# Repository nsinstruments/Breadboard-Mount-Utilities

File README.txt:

Breadboard Utilities
====================
This is a collection of utilities in the form of PCBs mounted on a breadboard,
which distributes power to each. I've used them for testing and development
over the last few years.

These are being released at your own risk, with no warranty or support, and
while they have been useful to me, New Systems Instruments does not warrant
their usefulness or fitness for any particular purpose or any other implied
warranty.

If you need help, please post in one of the usual public forums (discord, mw,
etc.) and @ me. I'm a helpful kind of human, so I might respond, but
unfortunately these aren't commercial products and I can't commit to always
giving support.

This work is licensed under the Creative Commons Attribution-ShareAlike 4.0
International License. To view a copy of this license, visit
http://creativecommons.org/licenses/by-sa/4.0/ or send a letter to Creative
Commons, PO Box 1866, Mountain View, CA 94042, USA.

A few things in here are the work of others, and AFAIK are freely
distributable and compatible with that license, but these retain their
original terms of distribution. I do not consider this a relicensing or any
alteration significant enough to claim some part of copyright on those files.

Since the DIY community is often considerate of personal wishes beyond the
official legal requirements, know that I'm perfectly happy for anyone who
wishes to build these for any purpose, personal commercial or otherwise, to
produce and distribute them to others, to fork the repository and offer
improvements, etc., as long as the terms of the above license are met. If
you're doing something that I might think is neat, or that I might want to
tell other people about, get in touch.

See the individual Read Me files for more details on each board.

Breadboard Compatibility
------------------------
This works with common 0.1" pitch breadboards. Note that AFAIK there is no
fixed standard for breadboards, so there is no guarantee it will work with any
particular breadboard. The most common incompatibility I've seen is where the
rail pins are not aligned with the main pins of the breadboard.

The power is put on the rails as follows:

-12 GND ... GND +12

As I have not seen any standard breadboard which is labeled this way, it is
recommended that you write over the +/- symbols on your breadboard with a
permanent marker to avoid confusion.

Some General Notes on Parts and Assembly
----------------------------------------
Distributors and part numbers are listed on each BOM, but none of this is
sacred; use your good sense to make substitutions as appropriate. In
particular, you might just want to buy some strips of breakable pin headers
rather than a bunch of different lengths.

In soldering these together, it's probably best to first solder the mounting
pins. I did this with the pins inserted in the breadboard, to make up for any
misalignments, but if you do that be careful not to put too much heat in and
melt the breadboard.

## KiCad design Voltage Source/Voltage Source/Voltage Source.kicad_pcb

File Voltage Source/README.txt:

Voltage Source
==============
This is a breadboard mounted dual precision voltage source, switchable between
0V, 3V, and 5v. It is designed to work with the breadboard mounted power
supply in this repository.

Power and Compatibility
-----------------------
This is designed to be powered by breadboard rails with the following
voltages:

-12 GND ... GND +12

This works with common 0.1" pitch breadboards. Note that AFAIK there is no
fixed standard for breadboards, so there is no guarantee it will work with any
particular breadboard. The most common incompatibility I've seen is where the
rail pins are not aligned with the main pins of the breadboard.

Calibration
-----------
This uses precise voltage sources and potentiometers to calibrate an output
voltage to very exact standards, within half a millivolt or so. You can
momentarily get better (within 10 microvolts), but this won't necessarily
stick around with with the mechanical settling of the trimmers or with
temperature changes. The resulting voltage will only be as accurate as your
multimeter, so make sure your multimeter will measure according to your
requirements. Go through each voltage one at a time, and turn the appropriate
potentiometer until the output is satisfactorily close to the nominal value.
You may get better accuracy by going through each voltage a second time, as
the voltage sources may shift very slightly with a slightly changing load.
This will also give the parts time to warm up to their typical operating
temperature. You might need to recalibrate as the trimmers settle.

Accuracy
---------
After calibration, there are three significant remaining sources of
inaccuracy. First, the voltage references themselves contribute a small
temperature dependency of 50ppm per degree C (or whatever is specified for the
particular part you are using). This figure is multiplied by the ratio of the
output voltage to the reference voltage (2.5V). Second, the potentiometers
contribute a temperature dependency. Last, the op amp offset and bias current
both have a temperature dependency. The op amp offset change with temperature
will be reproduced multiplied by the ratio of the output voltage to the
reference voltage. The op amp bias change with temperature will be reproduced
multiplied by the very large source resistors, so it is highly recommended
that you only use FET input op amps.

Resistor values
---------------
The calibration range is set by a resistor in series with the wiper of each
trimmer. These are chosen based on the accuracy of the resistors, op amp, and
voltage sources specified in the BOM. If you substitute components with lower
accuracies, you'll need to adjust the value of these resistors.

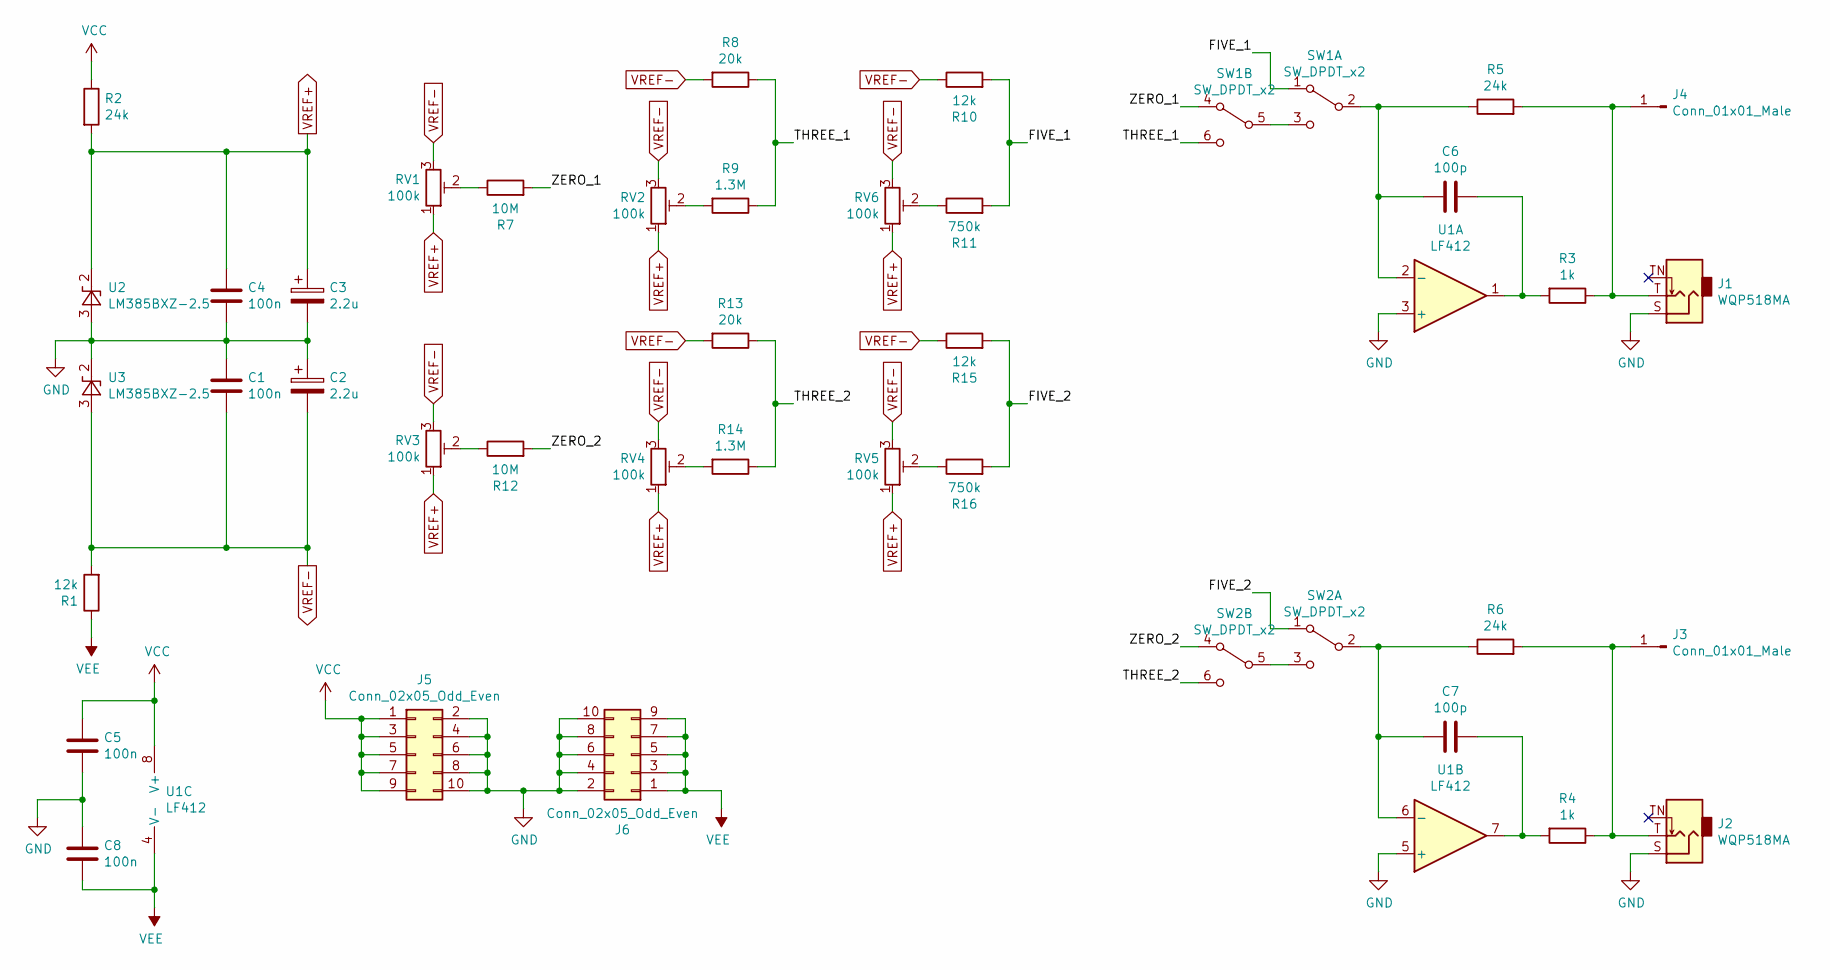
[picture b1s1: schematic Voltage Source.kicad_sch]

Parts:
C1, C4, C5, C8: 100n; C_Disc_D4.7mm_W2.5mm_P5.00mm
C2, C3: 2.2u; CP_Radial_D5.0mm_P2.00mm
C6, C7: 100p; C_Disc_D4.7mm_W2.5mm_P5.00mm
J1, J2: WQP518MA; QingPu_WQP518MA
J3, J4: Conn_01x01_Male; PinHeader_1x01_P2.54mm_Vertical
J5, J6: Conn_02x05_Odd_Even; PinHeader_2x05_P2.54mm_Vertical
R1, R10, R15: 12k; R_Axial_DIN0207_L6.3mm_D2.5mm_P2.54mm_Vertical
R2, R5, R6: 24k; R_Axial_DIN0207_L6.3mm_D2.5mm_P2.54mm_Vertical
R3, R4: 1k; R_Axial_DIN0207_L6.3mm_D2.5mm_P2.54mm_Vertical
R7, R12: 10M; R_Axial_DIN0207_L6.3mm_D2.5mm_P2.54mm_Vertical
R8, R13: 20k; R_Axial_DIN0207_L6.3mm_D2.5mm_P2.54mm_Vertical
R9, R14: 1.3M; R_Axial_DIN0207_L6.3mm_D2.5mm_P2.54mm_Vertical
R11, R16: 750k; R_Axial_DIN0207_L6.3mm_D2.5mm_P2.54mm_Vertical
RV1, RV2, RV3, RV4, RV5, RV6: 100k; Potentiometer_Bourns_3296Y_Vertical
SW1, SW2: SW_DPDT_x2; SW_Sub_DPDT
U1: LF412; DIP-8_W7.62mm
U2, U3: LM385BXZ-2.5; TO-92_Inline

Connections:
/FIVE_1: R10.2, R11.2, SW1.1 (A)
/FIVE_2: R15.2, R16.2, SW2.1 (A)
/THREE_1: R8.1, R9.1, SW1.6 (C)
/THREE_2: R13.1, R14.1, SW2.6 (C)
/ZERO_1: R7.2, SW1.4 (A)
/ZERO_2: R12.2, SW2.4 (A)
GND: C1.1, C2.1, C3.2, C4.2, C5.2, C8.1, J1.S, J2.S, J5.2, J5.4, J5.6, J5.8, J5.10, J6.2, J6.4, J6.6, J6.8, J6.10, U1.3 (+), U1.5 (+), U2.3 (A), U3.2 (K)
unnamed: C6.1, R3.2, U1.1
unnamed: C7.1, R4.2, U1.7
unnamed: J2.T, J3.1 (Pin_1_1), R4.1, R6.2
unnamed: J1.T, J4.1 (Pin_1_1), R3.1, R5.2
unnamed: R7.1, RV1.2
unnamed: R9.2, RV2.2
unnamed: R11.1, RV6.2
unnamed: R12.1, RV3.2
unnamed: R14.2, RV4.2
unnamed: R16.1, RV5.2
unnamed: C6.2, R5.1, SW1.2 (B), U1.2 (-)
unnamed: SW1.3 (C), SW1.5 (B)
unnamed: C7.2, R6.1, SW2.2 (B), U1.6 (-)
unnamed: SW2.3 (C), SW2.5 (B)
VCC: C5.1, J5.1, J5.3, J5.5, J5.7, J5.9, R2.1, U1.8 (V+)
VEE: C8.2, J6.1, J6.3, J6.5, J6.7, J6.9, R1.1, U1.4 (V-)
VREF+: C3.1, C4.1, R2.2, RV1.1, RV2.1, RV3.1, RV4.1, RV5.1, RV6.1, U2.2 (K)
VREF-: C1.2, C2.2, R1.2, R8.2, R10.1, R13.2, R15.1, RV1.3, RV2.3, RV3.3, RV4.3, RV5.3, RV6.3, U3.3 (A)

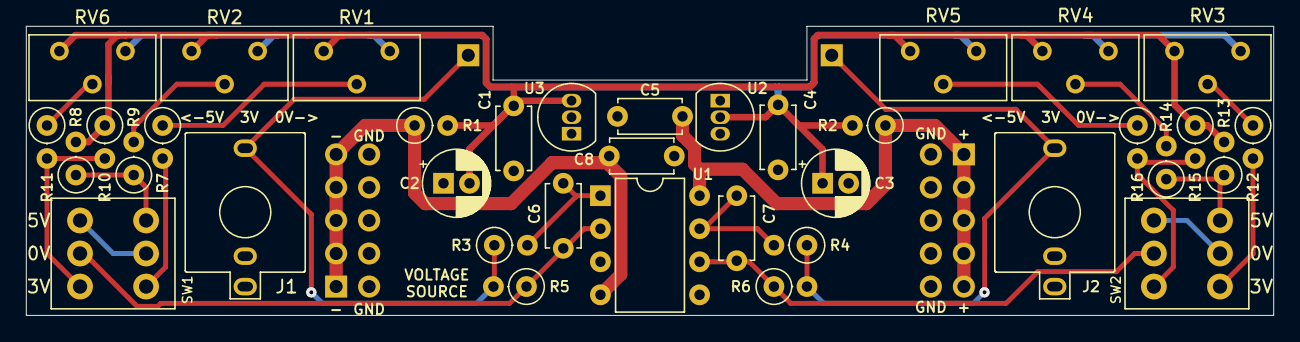
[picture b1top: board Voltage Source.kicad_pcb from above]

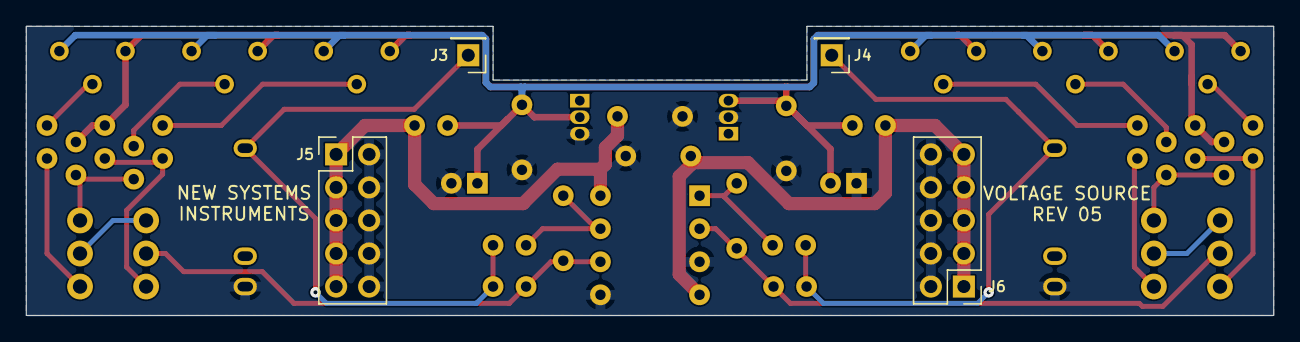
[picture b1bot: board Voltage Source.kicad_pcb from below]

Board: 2 copper layers, 95.9 x 22.2 mm, 41 parts (4 on the bottom side), 25 nets.

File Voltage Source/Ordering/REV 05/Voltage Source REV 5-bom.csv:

Reference,Value,Manufacturer,Part No.,Quantity
C1 C4 C5 C8,100n,Vishay,K104K15X7RF5TH5,4
C6 C7,100p,Vishay,K101J15C0GF5TH5,2
C2 C3,2.2u,Nichicon,UPS1V22 MDD,2
J3 J4,Conn_01x01_Male,Harwin,M20-9770242,1
J5 J6,Conn_02x05_Odd_Even,Harwin,M20-9760542,2
R1,12k,Yageo,MFR-25FRF52-12K,2
R3 R4,1k,Yageo,MFR-25FRF52-1K,2
R2 R5 R6,24k,Yageo,MFR-25FRF52-24K,2
R7 R12,10M,Yageo,HHV-25FR-52-10M,2
R8 R13,20k,Yageo,MFR-25FRF52-20K,2
R9 R14,1.3M,Yageo,MFR-25FRF52-1M3,2
R10 R15,12k,Yageo,MFR-25FRF52-12K,2
R11 R16,750k,Yageo,MFR-25FRF52-750K,2
RV1 RV2 RV3 RV4 RV5 RV6,100k,TT Electronics,67YR100K,6
U1,LF412,Texas Instruments,LF412CP,1
U2 U3,LM385BXZ-2.5,Texas Instruments,LM385BXZ-2.5/NOPB,2
,,,,
J1 J2,3.5mm Jack,Qing Pu,WQP518MA,2
SW1 SW2,DPDT,Taiway/Various,Sub-Miniature DPDT ON-ON-ON Toggle,2

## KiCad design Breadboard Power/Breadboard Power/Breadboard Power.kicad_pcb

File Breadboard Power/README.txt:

Breadboard Power
================
This is a power supply for a breadboard, providing +12V -12V and ground. It is
designed to be robust, simple, repairable, and safe.

Power Capabilities
------------------
This consists of a standard half-wave rectifier circuit powered from 12 VAC
from a wall wart power supply. Since the 12VAC is powering both the +12VDC and
-12VDC rail, the total current requirements will be roughly the sum of the
current on both rails. The recommended 500mA wall wart will provide about
200-250mA per rail before degrading. There is also a 1000mA wall wart
available that would be able to provide more current. However, consider
carefully whether you actually want your breadboard, or any wires sticking out
of it, to be able to deliver enough current to catch components on fire.

Noise and Precision
-------------------
This uses high quality linear LDO regulators and an AC input, resulting
in low ripple at 60Hz, without significant harmonic content at high
frequencies. I haven't done any robust measurements, but it seems to have
ripple within about 500uV at low loads, up to 1-2mV at high loads. So long as
the reservoir capacitor doesn't dip below the drop out ratings for the
regulators.

Compatibility and Location of the Rails
---------------------------------------
The power is put on the rails as follows:

-12 GND ... GND +12

As I have not seen any standard breadboard which is labeled this way, it is
recommended that you write over the +/- symbols on your breadboard with a
permanent marker.

This works with common 0.1" pitch breadboards. Note that AFAIK there is no
fixed standard for breadboards, so there is no guarantee it will work with any
particular breadboard. The most common incompatibility I've seen is where the
rail pins are not aligned with the main pins of the breadboard.

Safety
------
As a DIY project, I cannot possibly provide any guarantees that the finished
device will be safe. As with any unshielded electrical device, there is a small
risk of shock or fire under certain circumstances.

Nevertheless, this power supply is designed with safety and robustness in mind.
Resettable fuses placed between the reservoir capacitors and the regulators
will clamp down on overcurrents and shorts. If you trip them, unplug it, count
to 10, and plug it back in. Additionally, the regulators themselves have
internal current limiters that might catch on before the fuses. Additionally,
there are zeners to prevent overvoltage, which, depending on how bad the
overvoltage is, will trip those same fuses. And of course the power itself is
coming from the isolated secondary of a transformer.

Ordering and Assembly
---------------------
I won't go into details here. Just a few notes.

* The large capacitors are 3300uF or 3.3mF. The capacitance and ESR is lightly
  related to efficiency and how close to the rated current you can go, but the
  exact value is not particularly important.

* The rectifier diodes are Schottkys, as otherwise the LDOs can get starved
  too easily. The voltage each diode sees is rail to rail at the supply
  capacitors, so don't skimp on a lower breakdown voltage.

* The LEDs are low current, and the resistors into them give very low current,
  resulting in just enough brightness so you can tell that they're on. This
  "barely on" is intentional behavior to lower eye strain when looking at the
  breadboard, but if you want them to be brighter, just lower the value of the
  resistors by half or so. Note that if you substitute higher current LEDs, you might need
  lower value resistors for the LEDs to be visible at all.

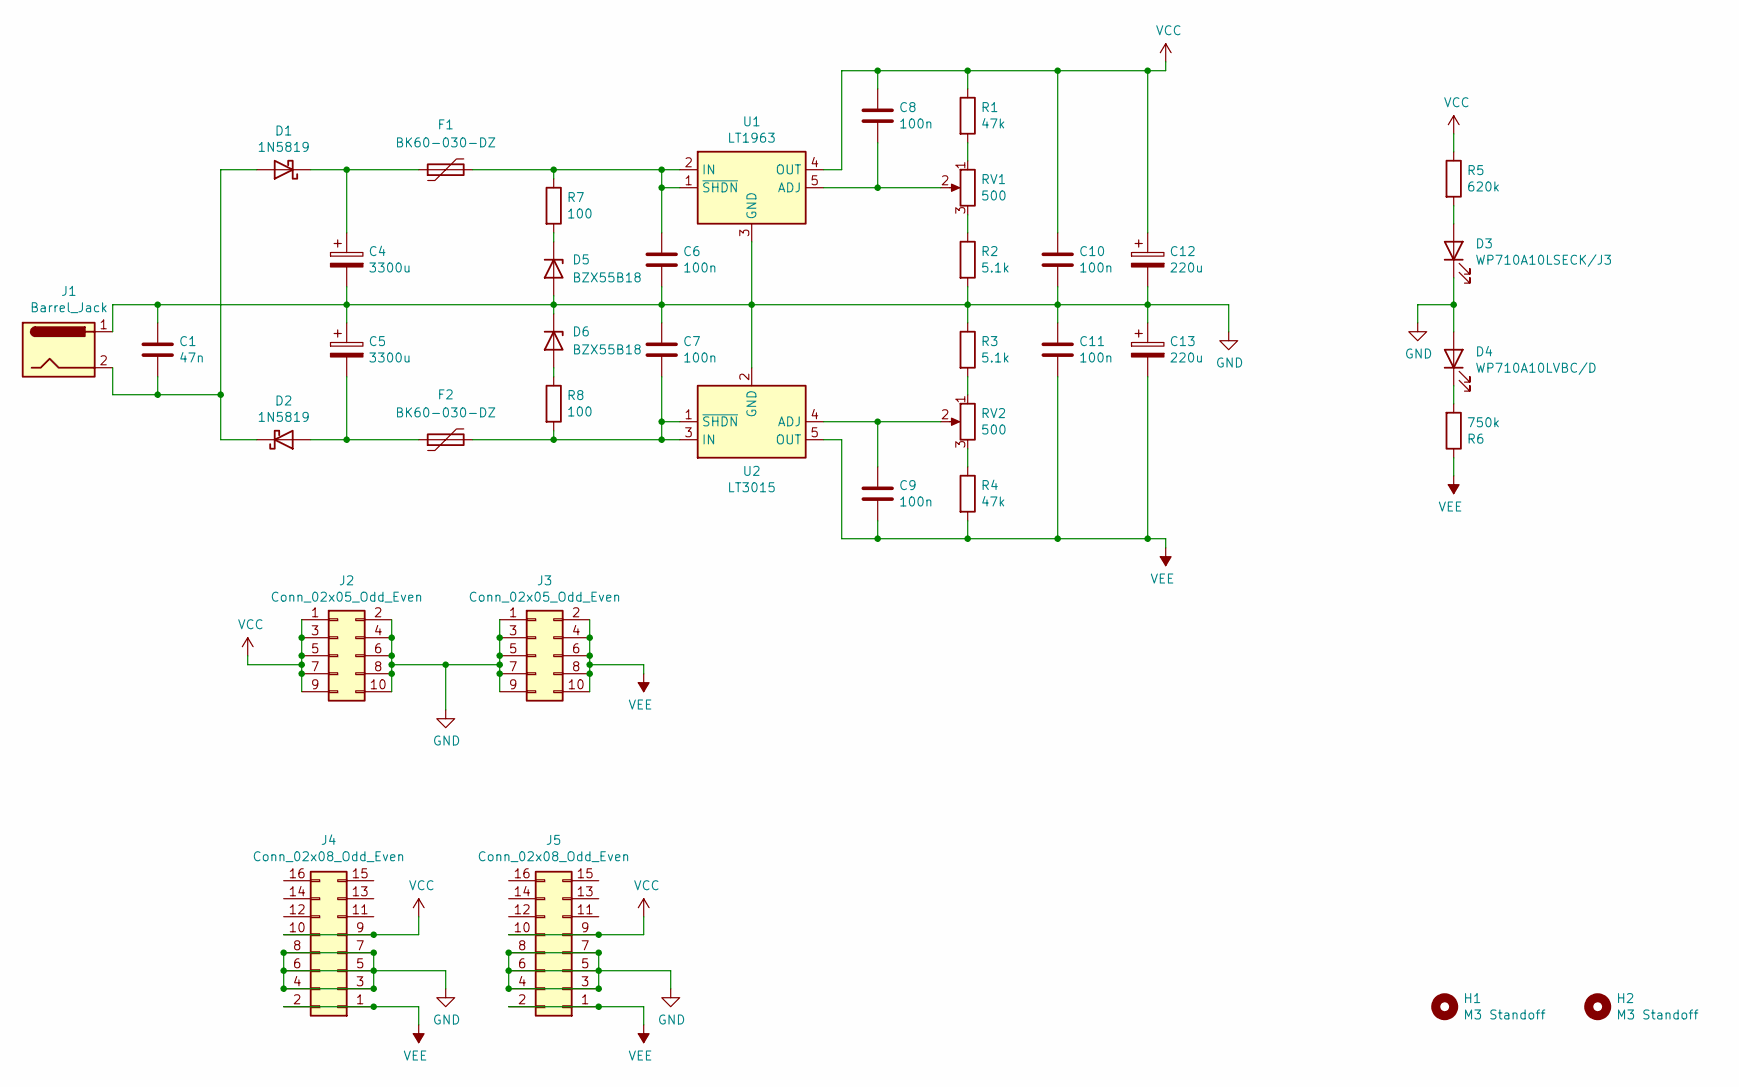
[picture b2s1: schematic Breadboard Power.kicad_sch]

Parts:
C1: 47n; C_Disc_D4.7mm_W2.5mm_P5.00mm
C4, C5: 3300u; CP_Radial_D16.0mm_P7.50mm
C6, C7, C8, C9, C10, C11: 100n; C_Disc_D5.0mm_W2.5mm_P5.00mm
C12, C13: 220u; CP_Radial_D8.0mm_P3.50mm
D1, D2: 1N5819; D_DO-41_SOD81_P7.62mm_Horizontal
D3: WP710A10LSECK/J3; LED_D3.0mm
D4: WP710A10LVBC/D; LED_D3.0mm
D5, D6: BZX55B18; D_DO-35_SOD27_P7.62mm_Horizontal
F1, F2: BK60-030-DZ; C_Disc_D7.5mm_W2.5mm_P5.00mm
H1, H2: M3 Standoff; MountingHole_3.2mm_M3_Pad
J1: Barrel_Jack; BarrelJack_Horizontal
J2, J3: Conn_02x05_Odd_Even; PinHeader_2x05_P2.54mm_Vertical
J4, J5: Conn_02x08_Odd_Even; IDC-Header_2x08_P2.54mm_Vertical
R1, R4: 47k; R_Axial_DIN0207_L6.3mm_D2.5mm_P7.62mm_Horizontal
R2, R3: 5.1k; R_Axial_DIN0207_L6.3mm_D2.5mm_P7.62mm_Horizontal
R5: 620k; R_Axial_DIN0207_L6.3mm_D2.5mm_P7.62mm_Horizontal
R6: 750k; R_Axial_DIN0207_L6.3mm_D2.5mm_P7.62mm_Horizontal
R7, R8: 100; R_Axial_DIN0207_L6.3mm_D2.5mm_P7.62mm_Horizontal
RV1, RV2: 500; Potentiometer_Bourns_3296Y_Vertical
U1: LT1963; TO-220-5_P3.4x3.7mm_StaggerOdd_Lead3.8mm_Vertical
U2: LT3015; TO-220-5_P3.4x3.7mm_StaggerOdd_Lead3.8mm_Vertical

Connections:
GND: C1.1, C4.2, C5.1, C6.2, C7.1, C10.2, C11.1, C12.2, C13.1, D3.1 (K), D4.2 (A), D5.2 (A), D6.1 (K), J1.1, J2.2, J2.4, J2.6, J2.8, J2.10, J3.1, J3.3, J3.5, J3.7, J3.9, J4.3, J4.4, J4.5, J4.6, J4.7, J4.8, J5.3, J5.4, J5.5, J5.6, J5.7, J5.8, R2.2, R3.1, U1.3 (GND), U2.2 (GND)
unnamed: C1.2, D1.2 (A), D2.1 (K), J1.2
unnamed: C4.1, D1.1 (K), F1.1
unnamed: C5.2, D2.2 (A), F2.1
unnamed: D3.2 (A), R5.2
unnamed: D4.1 (K), R6.2
unnamed: D5.1 (K), R7.2
unnamed: D6.2 (A), R8.1
unnamed: R1.2, RV1.1
unnamed: R2.1, RV1.3
unnamed: R3.2, RV2.1
unnamed: R4.1, RV2.3
unnamed: C8.2, RV1.2, U1.5 (ADJ)
unnamed: C6.1, F1.2, R7.1, U1.1 (~SHDN), U1.2 (IN)
unnamed: C9.1, RV2.2, U2.4 (ADJ)
unnamed: C7.2, F2.2, R8.2, U2.1 (~SHDN), U2.3 (IN)
VCC: C8.1, C10.1, C12.1, J2.1, J2.3, J2.5, J2.7, J2.9, J4.9, J4.10, J5.9, J5.10, R1.1, R5.1, U1.4 (OUT)
VEE: C9.2, C11.2, C13.2, J3.2, J3.4, J3.6, J3.8, J3.10, J4.1, J4.2, J5.1, J5.2, R4.2, R6.1, U2.5 (OUT)

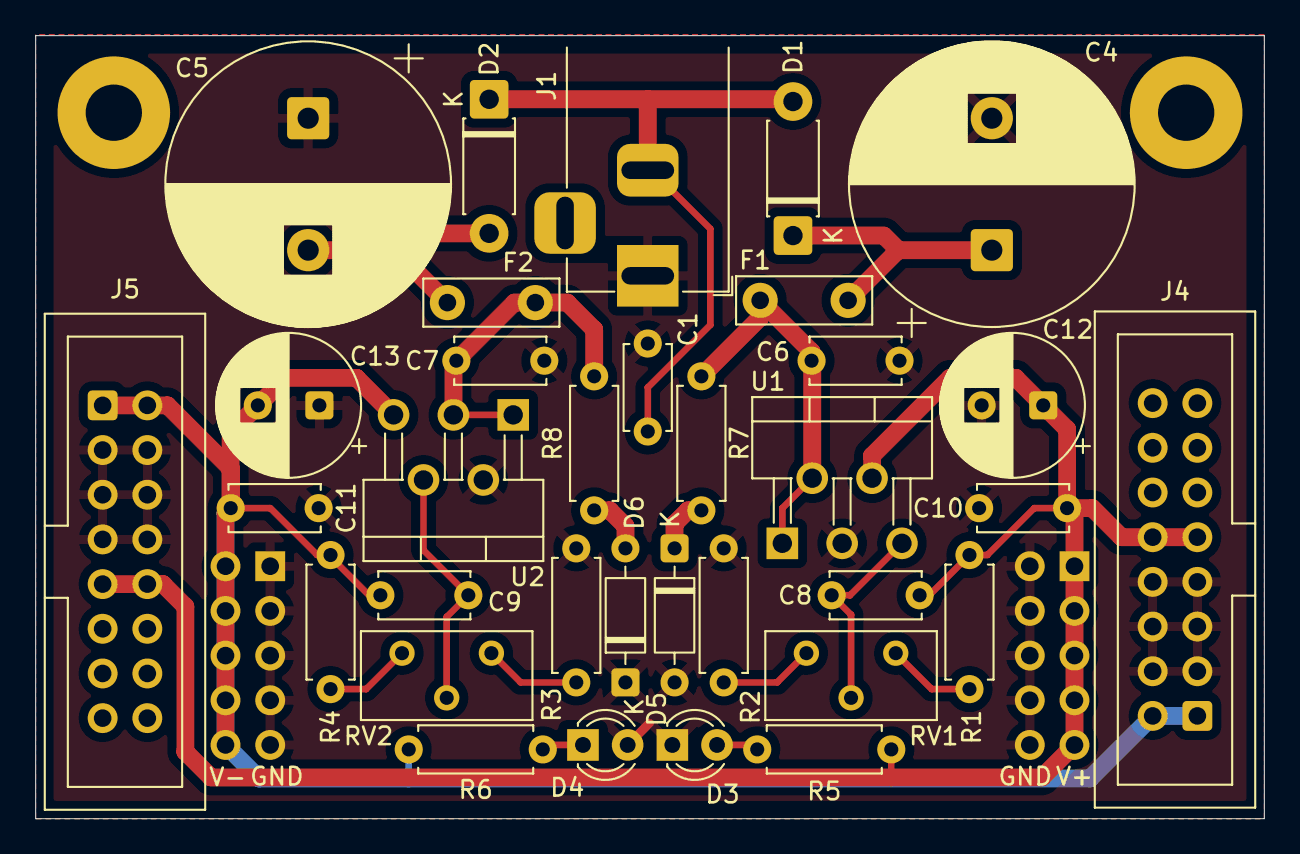
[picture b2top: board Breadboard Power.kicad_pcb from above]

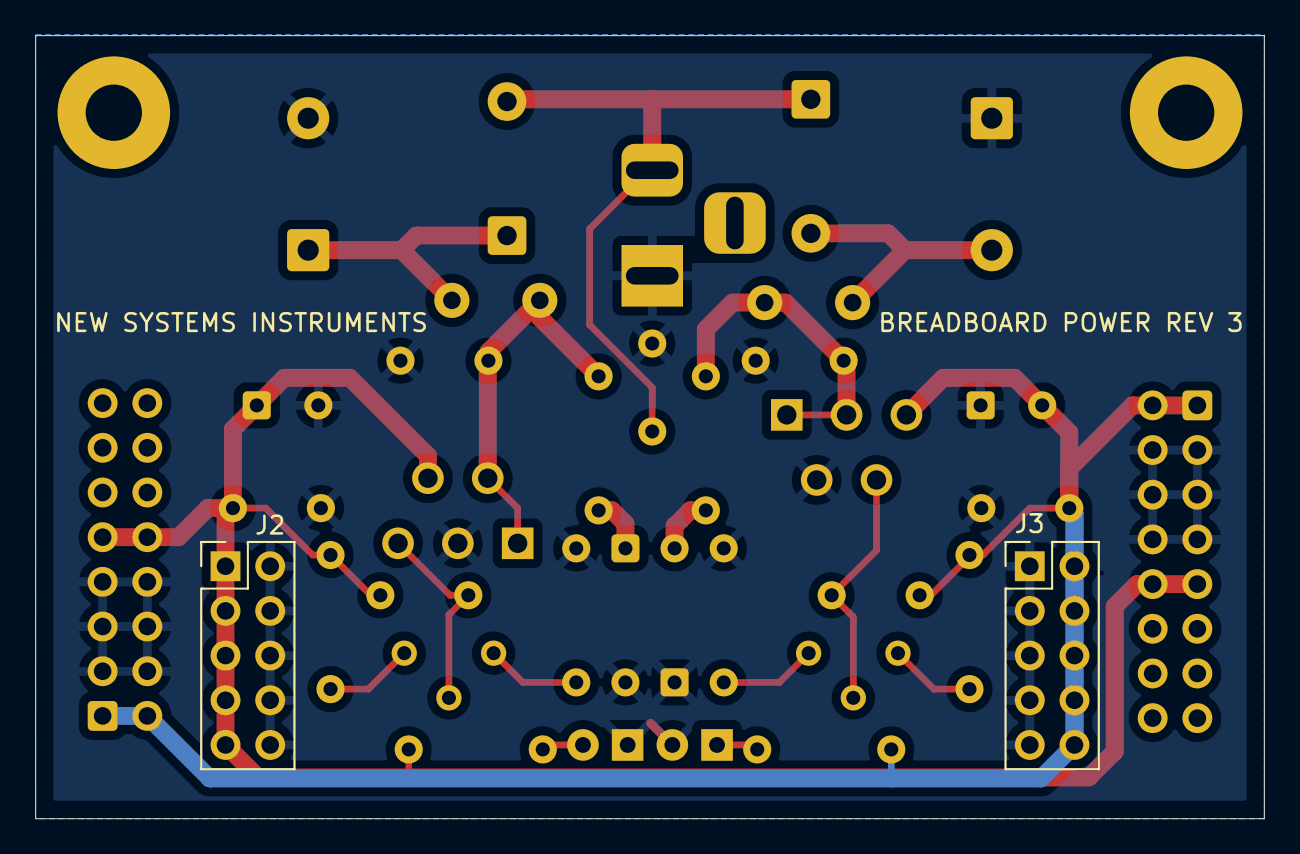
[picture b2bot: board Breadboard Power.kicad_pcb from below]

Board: 2 copper layers, 69.8 x 44.5 mm, 38 parts (2 on the bottom side), 18 nets.

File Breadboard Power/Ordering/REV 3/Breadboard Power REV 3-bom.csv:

Reference,Value,Footprint,Manufacturer,Part No.,Quantity
C1,47n,Capacitor_THT:C_Disc_D4.7mm_W2.5mm_P5.00mm,Vishay,K473K15X7RF5TH5,1
C4 C5,3300u,Capacitor_THT:CP_Radial_D16.0mm_P7.50mm,Nichicon,UPJ1E332MHD,2
C6 C7 C8 C9 C10 C11,100n,Capacitor_THT:C_Disc_D5.0mm_W2.5mm_P5.00mm,Vishay,K104K15X7RF5TH5,6
C12 C13,220u,Capacitor_THT:CP_Radial_D8.0mm_P3.50mm,Nichicon,UPS1E221MPD,2
D1 D2,1N5819,Diode_THT:D_DO-41_SOD81_P7.62mm_Horizontal,ON Semiconductor,1N5819G,2
D3,WP710A10LSECK/J3,LED_THT:LED_D3.0mm,Kingbright,WP710A10LSECK/J3,1
D4,WP710A10LVBC/D,LED_THT:LED_D3.0mm,Kingbright,WP710A10LVBC/D,1
D5 D6,BZX55B18,Diode_THT:D_DO-35_SOD27_P7.62mm_Horizontal,Vishay,BZX55B18,2
F1 F2,BK60-030-DZ,Capacitor_THT:C_Disc_D7.5mm_W2.5mm_P5.00mm,Yageo,BK60-030-DZ,2
J1,Barrel_Jack,Connector_BarrelJack:BarrelJack_Horizontal,Kobiconn,163-179PH-EX,1
J2 J3,Conn_02x05_Odd_Even,Connector_PinHeader_2.54mm:PinHeader_2x05_P2.54mm_Vertical,Harwin,M20-9760542,2
J4 J5,Conn_02x08_Odd_Even,Connector_IDC:IDC-Header_2x08_P2.54mm_Vertical,Adam Tech,BHR-16-VUA,2
R1 R4,47k,Resistor_THT:R_Axial_DIN0207_L6.3mm_D2.5mm_P7.62mm_Horizontal,Yageo,MFR-25FRF52-47K,2
R2 R3,5.1k,Resistor_THT:R_Axial_DIN0207_L6.3mm_D2.5mm_P7.62mm_Horizontal,Yageo,MFR-25FRF52-5K1,2
R5,620k,Resistor_THT:R_Axial_DIN0207_L6.3mm_D2.5mm_P7.62mm_Horizontal,Yageo,MFR-25FRF52-620K,1
R6,750k,Resistor_THT:R_Axial_DIN0207_L6.3mm_D2.5mm_P7.62mm_Horizontal,Yageo,MFR-25FRF52-750K,1
R7 R8,100,Resistor_THT:R_Axial_DIN0207_L6.3mm_D2.5mm_P7.62mm_Horizontal,Yageo,MFR-25FRF52-100R,2
RV1 RV2,500,Potentiometer_THT:Potentiometer_Bourns_3296Y_Vertical,TT Electronics,67YR500,2
U1,LT1963,Package_TO_SOT_THT:TO-220-5_P3.4x3.7mm_StaggerOdd_Lead3.8mm_Vertical,Analog Devices Inc.,LT1963ET#PBF,1
U2,LT3015,Package_TO_SOT_THT:TO-220-5_P3.4x3.7mm_StaggerOdd_Lead3.8mm_Vertical,Analog Devices Inc.,LT3015ET#PBF,1
,12 mm M3 standoffs,,Keystone Electronics,24434,2
,6mm M3 screws,,Keystone Electronics,29311,2
,12 VAC power supply,,Triad,WAU12-500,1

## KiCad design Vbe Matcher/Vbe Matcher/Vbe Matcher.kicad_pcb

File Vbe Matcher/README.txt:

Vbe Matcher
===========
This is a simple widget to match the Vbe on two bipolar transistors. 

Theory of Operation
-------------------
See the document by Ian Fritz in this repository.

Caveat Emptor
-------------
This circuit adequately reproduces the Ian Fritz circuit described in the
paper, along with the added trimmer. If we were breadboarding this circuit,
that would be the end of it. However, given that it's a PCB, practically there
are quite a few nice things that could have been done but weren't. For
example, there could be posts to clip an alligator clip for a multimeter, thus
saving one or two of your four hands. It works, but it isn't streamlined for
ease of use. One of the nice things about the Ian Fritz circuit, however, is
that it's intuitive and simple and easy to understand and modify.

Another thing that I should mention is that you should consider whether the
transistors in question need to have the same Vbe or just the same Vt, or
temperature dependency. Proximity gives you the same Vt, and you don't need to
match. In my case, Vt is usually the important part, and so I don't use this
circuit very often.

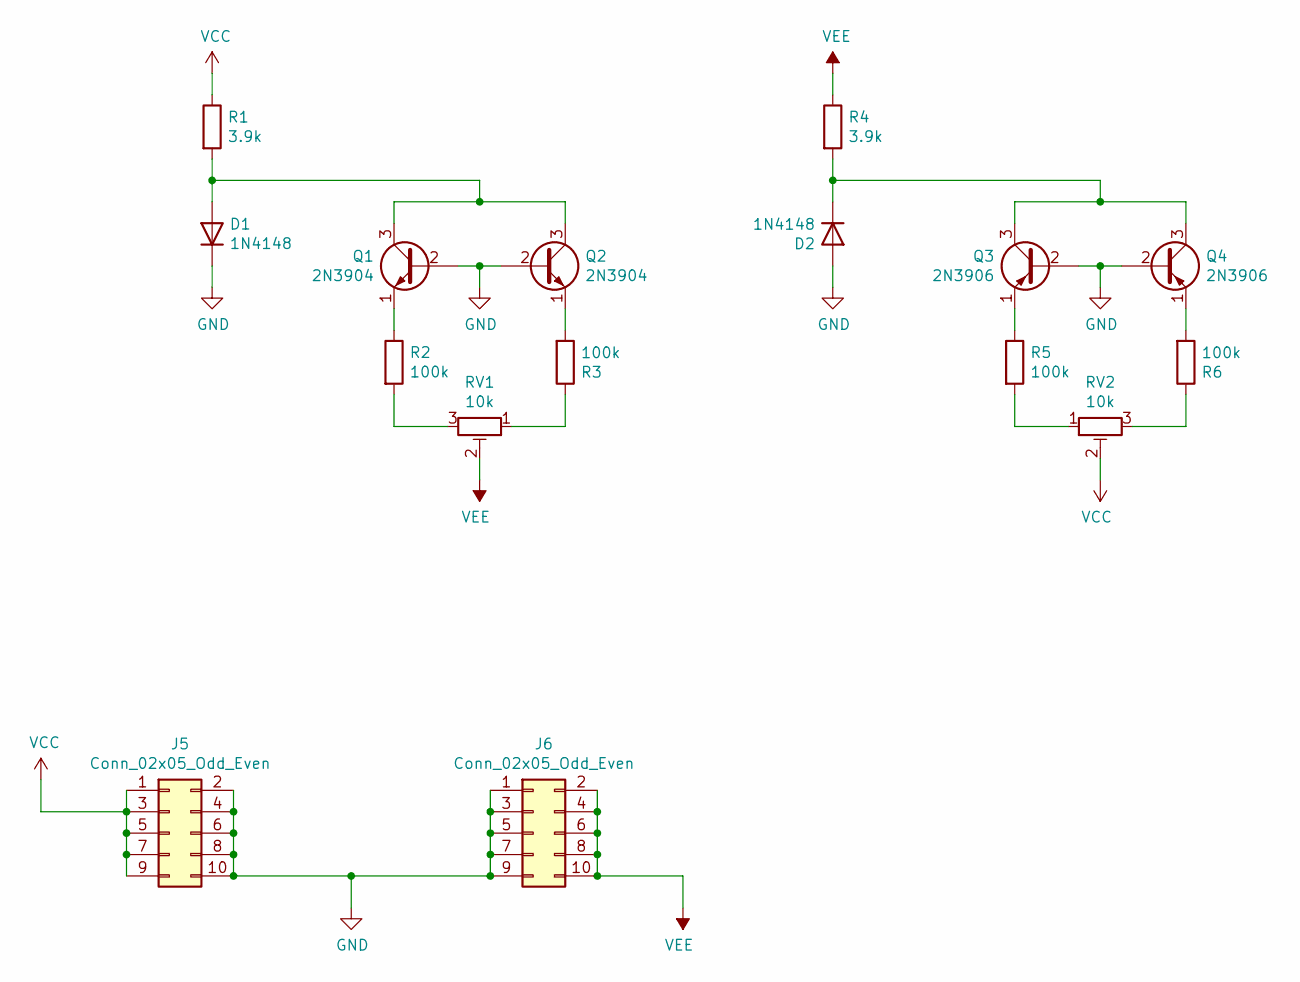
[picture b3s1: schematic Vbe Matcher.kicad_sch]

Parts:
D1, D2: 1N4148; D_DO-35_SOD27_P7.62mm_Horizontal
J5, J6: Conn_02x05_Odd_Even; PinHeader_2x05_P2.54mm_Vertical
Q1, Q2: 2N3904; TO-92_Inline_Wide
Q3, Q4: 2N3906; TO-92_Inline_Wide
R1, R4: 3.9k; R_Axial_DIN0207_L6.3mm_D2.5mm_P7.62mm_Horizontal
R2, R3, R5, R6: 100k; R_Axial_DIN0207_L6.3mm_D2.5mm_P2.54mm_Vertical
RV1, RV2: 10k; Pot_TT_36F

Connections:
GND: D1.1 (K), D2.2 (A), J5.2, J5.4, J5.6, J5.8, J5.10, J6.1, J6.3, J6.5, J6.7, J6.9, Q1.2 (B), Q2.2 (B), Q3.2 (B), Q4.2 (B)
unnamed: D1.2 (A), Q1.3 (C), Q2.3 (C), R1.2
unnamed: D2.1 (K), Q3.3 (C), Q4.3 (C), R4.2
unnamed: Q1.1 (E), R2.1
unnamed: Q2.1 (E), R3.2
unnamed: Q3.1 (E), R5.1
unnamed: Q4.1 (E), R6.2
unnamed: R2.2, RV1.3
unnamed: R3.1, RV1.1
unnamed: R5.2, RV2.1
unnamed: R6.1, RV2.3
VCC: J5.1, J5.3, J5.5, J5.7, J5.9, R1.1, RV2.2
VEE: J6.2, J6.4, J6.6, J6.8, J6.10, R4.1, RV1.2

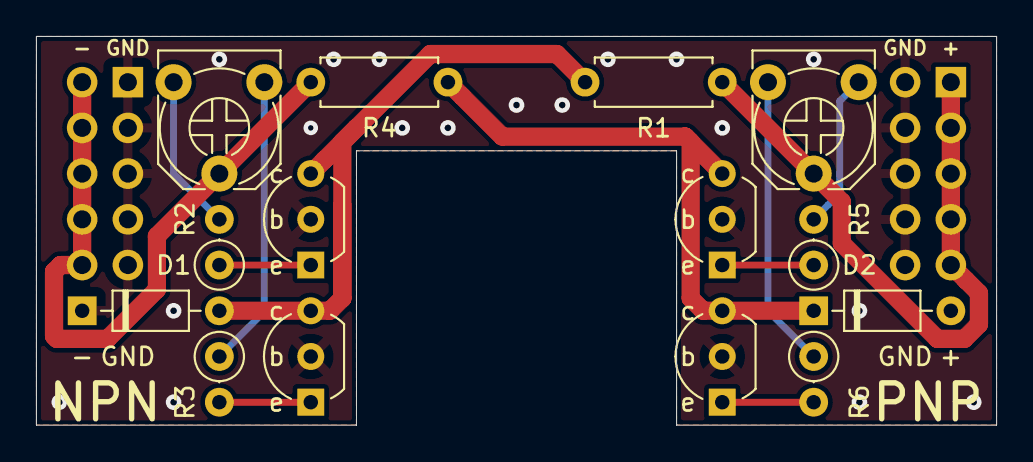
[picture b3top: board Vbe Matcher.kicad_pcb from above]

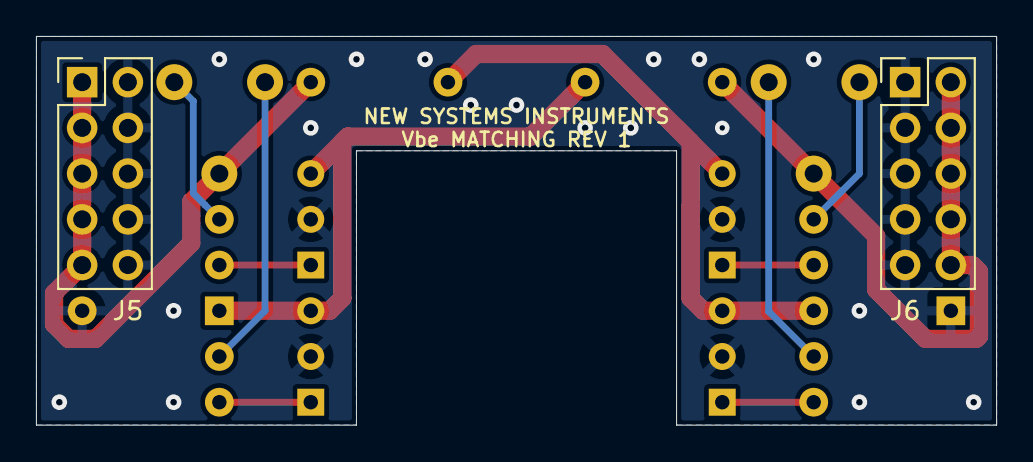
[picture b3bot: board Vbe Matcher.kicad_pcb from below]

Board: 2 copper layers, 53.3 x 21.6 mm, 16 parts (2 on the bottom side), 13 nets.

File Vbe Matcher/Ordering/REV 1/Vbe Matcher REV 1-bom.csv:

Reference,Value,Distributor,Manufacturer,Part No.,Quantity,Price
D1 D2 ,1N4148,Mouser/Digi-Key,ON Semiconductor,1N4148,2,$0.10
J5 J6 ,Conn_02x05_Odd_Even,Mouser/Digi-Key,Harwin,M20-9760542,2,$0.43
Jx,Conn_01x06,Mouser/Digi-Key,Harwin,M20-9770742,2,$0.51
R1 R4 ,3.9k,Mouser/Digi-Key,Yageo,MFR-25FRF52-3K9,2,$0.10
R2 R3 R5 R6 ,100k,Mouser/Digi-Key,Yageo,MFR-25FRF52-100K,4,$0.12
RV1 RV2 ,10k,Mouser/Digi-Key,Bourns,3306F-1-103,2,$0.43

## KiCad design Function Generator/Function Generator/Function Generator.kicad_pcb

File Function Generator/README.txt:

Function Generator
==================
This is a simple breadboard mounted dual function generator, with a range of
3.5 minute cycles to 20kHz and a triangle and square wave output. It is
designed to work with the breadboard mounted power supply in this repository.

Power and Compatibility
-----------------------
This is designed to be powered by breadboard rails with the following
voltages:

-12 GND ... GND +12

This works with common 0.1" pitch breadboards. Note that AFAIK there is no
fixed standard for breadboards, so there is no guarantee it will work with any
particular breadboard. The most common incompatibility I've seen is where the
rail pins are not aligned with the main pins of the breadboard.

Notes on Components
-------------------
* The ceramic capacitors used in the oscillator must be C0G/NP0, but could be
  replaced by film capacitors if they match the footprint.
* The electrolytic capacitors used in the oscillator are bipolar. Unlike in a
  decoupling application, in this circuit a polarized electrolytic would fail,
  possibly rupturing violently.

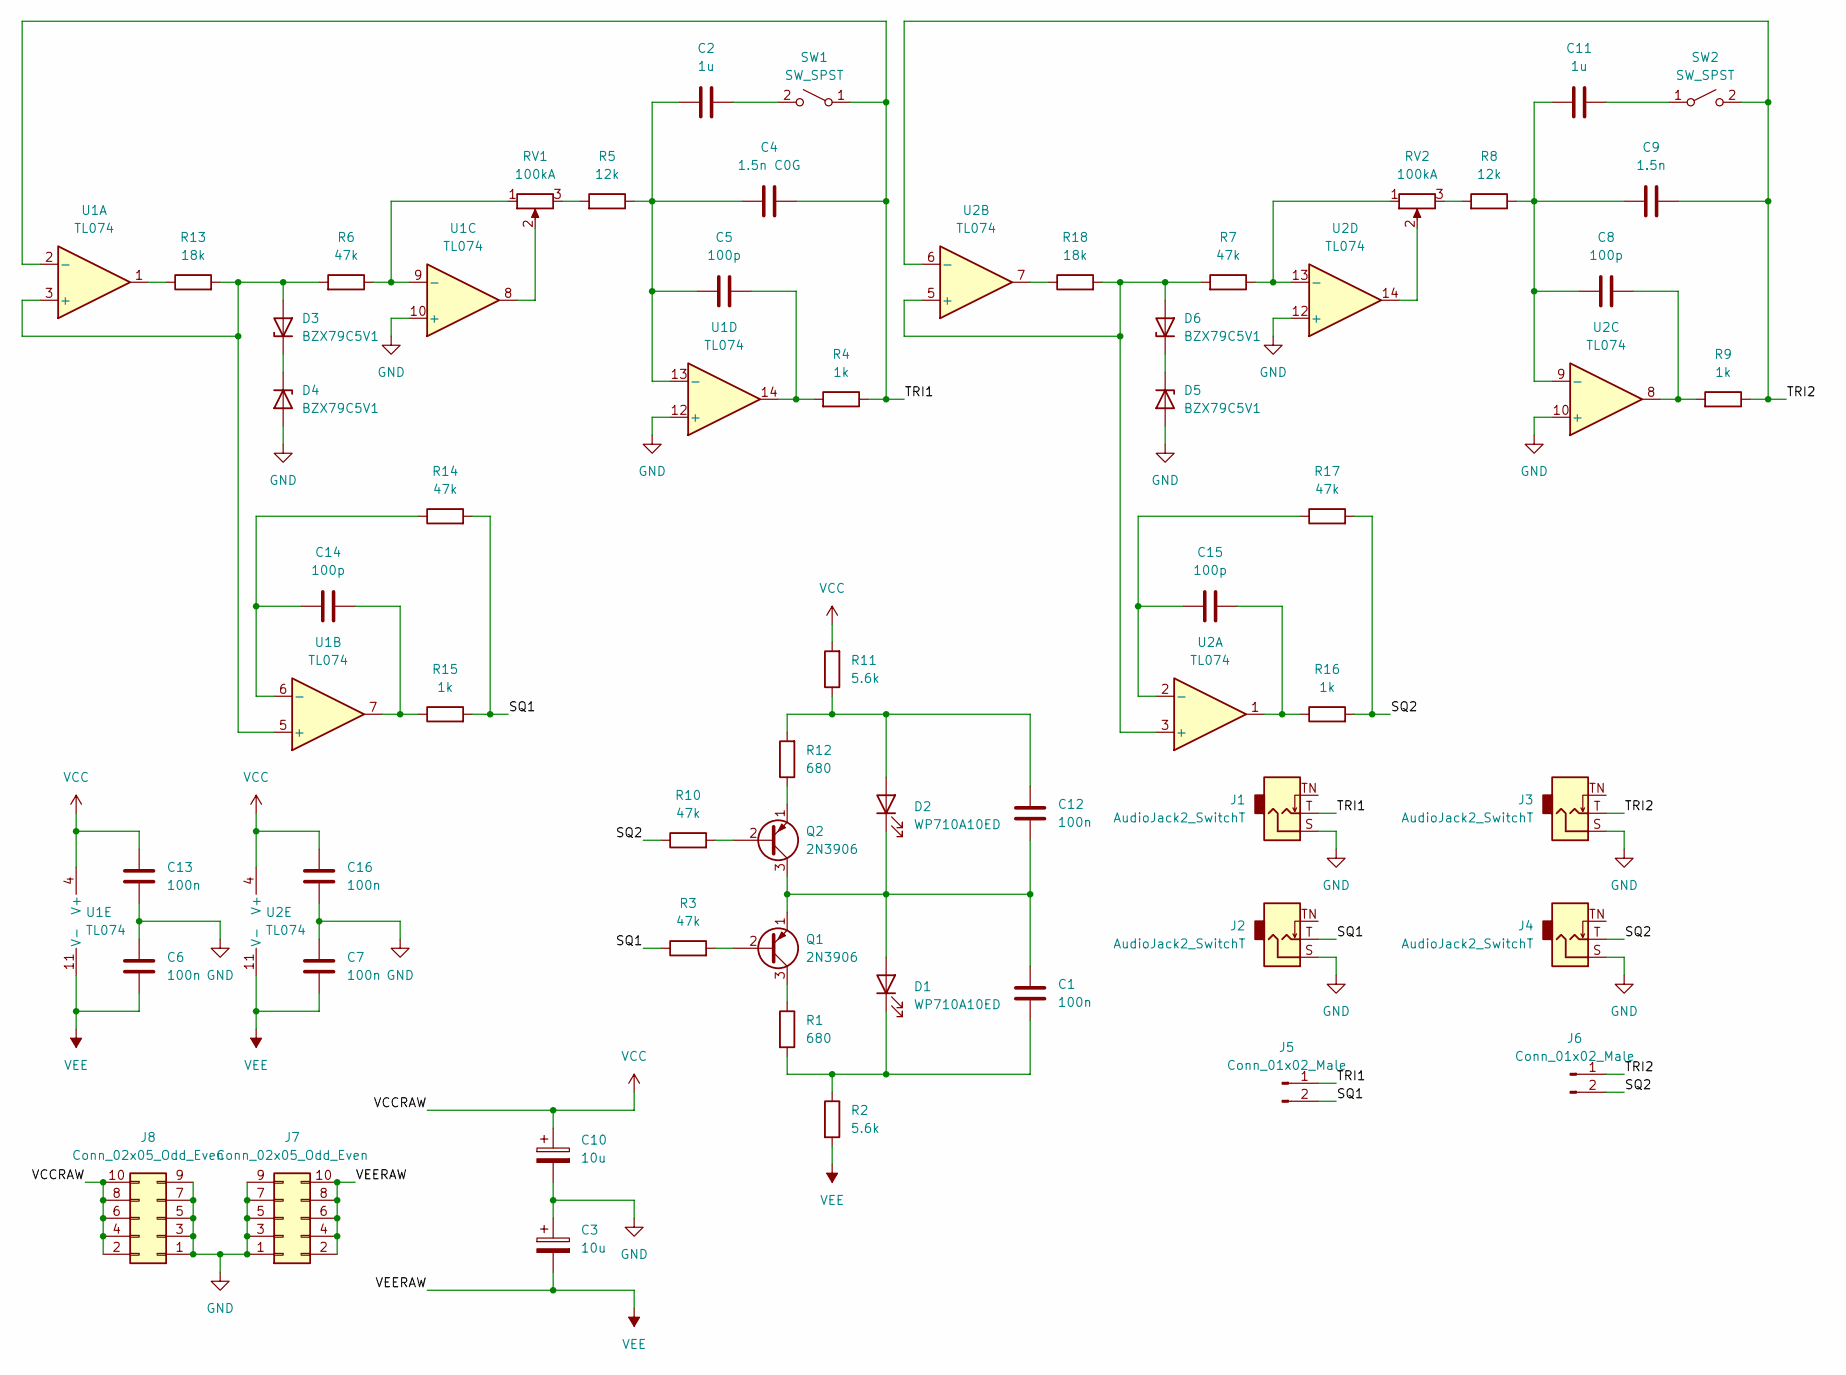
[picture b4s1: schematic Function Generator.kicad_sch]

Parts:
C1, C6, C7, C12, C13, C16: 100n; C_Disc_D4.7mm_W2.5mm_P5.00mm
C2, C11: 1u; C_Radial_D5.0mm_H11.0mm_P2.00mm
C3, C10: 10u; CP_Radial_D5.0mm_P2.00mm
C4: 1.5n C0G; C_Disc_D4.7mm_W2.5mm_P5.00mm
C5, C8, C14, C15: 100p; C_Disc_D4.7mm_W2.5mm_P5.00mm
C9: 1.5n; C_Disc_D4.7mm_W2.5mm_P5.00mm
D1, D2: WP710A10ED; LED_D3.0mm-2
D3, D4, D5, D6: BZX79C5V1; D_DO-35_SOD27_P2.54mm_Vertical_KathodeUp
J1, J2, J3, J4: AudioJack2_SwitchT; QingPu_WQP518MA
J5, J6: Conn_01x02_Male; PinHeader_1x02_P2.54mm_Vertical
J7, J8: Conn_02x05_Odd_Even; PinHeader_2x05_P2.54mm_Vertical
Q1, Q2: 2N3906; TO-92_Inline
R1, R12: 680; R_Axial_DIN0207_L6.3mm_D2.5mm_P2.54mm_Vertical
R2, R11: 5.6k; R_Axial_DIN0207_L6.3mm_D2.5mm_P2.54mm_Vertical
R3, R6, R7, R10, R14, R17: 47k; R_Axial_DIN0207_L6.3mm_D2.5mm_P2.54mm_Vertical
R4, R9, R15, R16: 1k; R_Axial_DIN0207_L6.3mm_D2.5mm_P2.54mm_Vertical
R5: 12k; R_Axial_DIN0207_L6.3mm_D2.5mm_P2.54mm_Vertical
R8: 12k; R_Axial_DIN0207_L6.3mm_D2.5mm_P7.62mm_Horizontal
R13, R18: 18k; R_Axial_DIN0207_L6.3mm_D2.5mm_P2.54mm_Vertical
RV1, RV2: 100kA; Potentiometer_Alpha_RD901F-40
SW1, SW2: SW_SPST; SW_Taiway_Sub_SPDT
U1, U2: TL074; DIP-14_W7.62mm

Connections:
/SQ1: J2.T, J5.2, R3.1, R14.2, R15.2
/SQ2: J4.T, J6.2, R10.1, R16.2, R17.2
/TRI1: C4.2, J1.T, J5.1, R4.1, SW1.1 (A), U1.2 (-)
/TRI2: C9.2, J3.T, J6.1, R9.1, SW2.2 (B), U2.6 (-)
GND: C3.1, C6.1, C7.1, C10.2, C13.2, C16.2, D4.2 (A), D5.2 (A), J1.S, J2.S, J3.S, J4.S, J7.1, J7.3, J7.5, J7.7, J7.9, J8.1, J8.3, J8.5, J8.7, J8.9, U1.10 (+), U1.12 (+), U2.10 (+), U2.12 (+)
unnamed: C1.2, D1.1 (K), R1.2, R2.1
unnamed: C2.2, SW1.2 (B)
unnamed: C2.1, C4.1, C5.1, R5.1, U1.13 (-)
unnamed: C5.2, R4.2, U1.14
unnamed: C8.1, C9.1, C11.1, R8.1, U2.9 (-)
unnamed: C8.2, R9.2, U2.8
unnamed: C11.2, SW2.1 (A)
unnamed: C12.1, D2.2 (A), R11.1, R12.2
unnamed: C1.1, C12.2, D1.2 (A), D2.1 (K), Q1.1 (E), Q2.3 (C)
unnamed: C14.1, R14.1, U1.6 (-)
unnamed: C14.2, R15.1, U1.7
unnamed: C15.1, R17.1, U2.2 (-)
unnamed: C15.2, R16.1, U2.1
unnamed: D3.1 (K), D4.1 (K)
unnamed: D3.2 (A), R6.2, R13.2, U1.3 (+), U1.5 (+)
unnamed: D5.1 (K), D6.1 (K)
unnamed: D6.2 (A), R7.2, R18.2, U2.3 (+), U2.5 (+)
unnamed: Q1.2 (B), R3.2
unnamed: Q1.3 (C), R1.1
unnamed: Q2.1 (E), R12.1
unnamed: Q2.2 (B), R10.2
unnamed: R5.2, RV1.3
unnamed: R6.1, RV1.1, U1.9 (-)
unnamed: R7.1, RV2.1, U2.13 (-)
unnamed: R8.2, RV2.3
unnamed: R13.1, U1.1
unnamed: R18.1, U2.7
unnamed: RV1.2, U1.8
unnamed: RV2.2, U2.14
VCC: C10.1, C13.1, C16.1, J8.2, J8.4, J8.6, J8.8, J8.10, R11.2, U1.4 (V+), U2.4 (V+)
VEE: C3.2, C6.2, C7.2, J7.2, J7.4, J7.6, J7.8, J7.10, R2.2, U1.11 (V-), U2.11 (V-)
